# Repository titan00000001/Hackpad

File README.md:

# Arrowpad

My hackpad keyboard is a Macropad to mimic the Arrow keys to be like a controller for keyboard games

## Features
- Can be used as arrows on Keyboard
- Mini Keyboard like design to make it seem like a small keyboard

## Schematics

## PCB

## Assembly

## BOM

| Qty | Part Name               |
|-----|-------------------------|
| 4   | Switches                |
| 4   | Keycaps                 |
| 2   | LEDs                    |
| 1   | Seeed XIAO RP2040       |
| 1   | Case (3d-printed)       |
| 1   | PCB                     |

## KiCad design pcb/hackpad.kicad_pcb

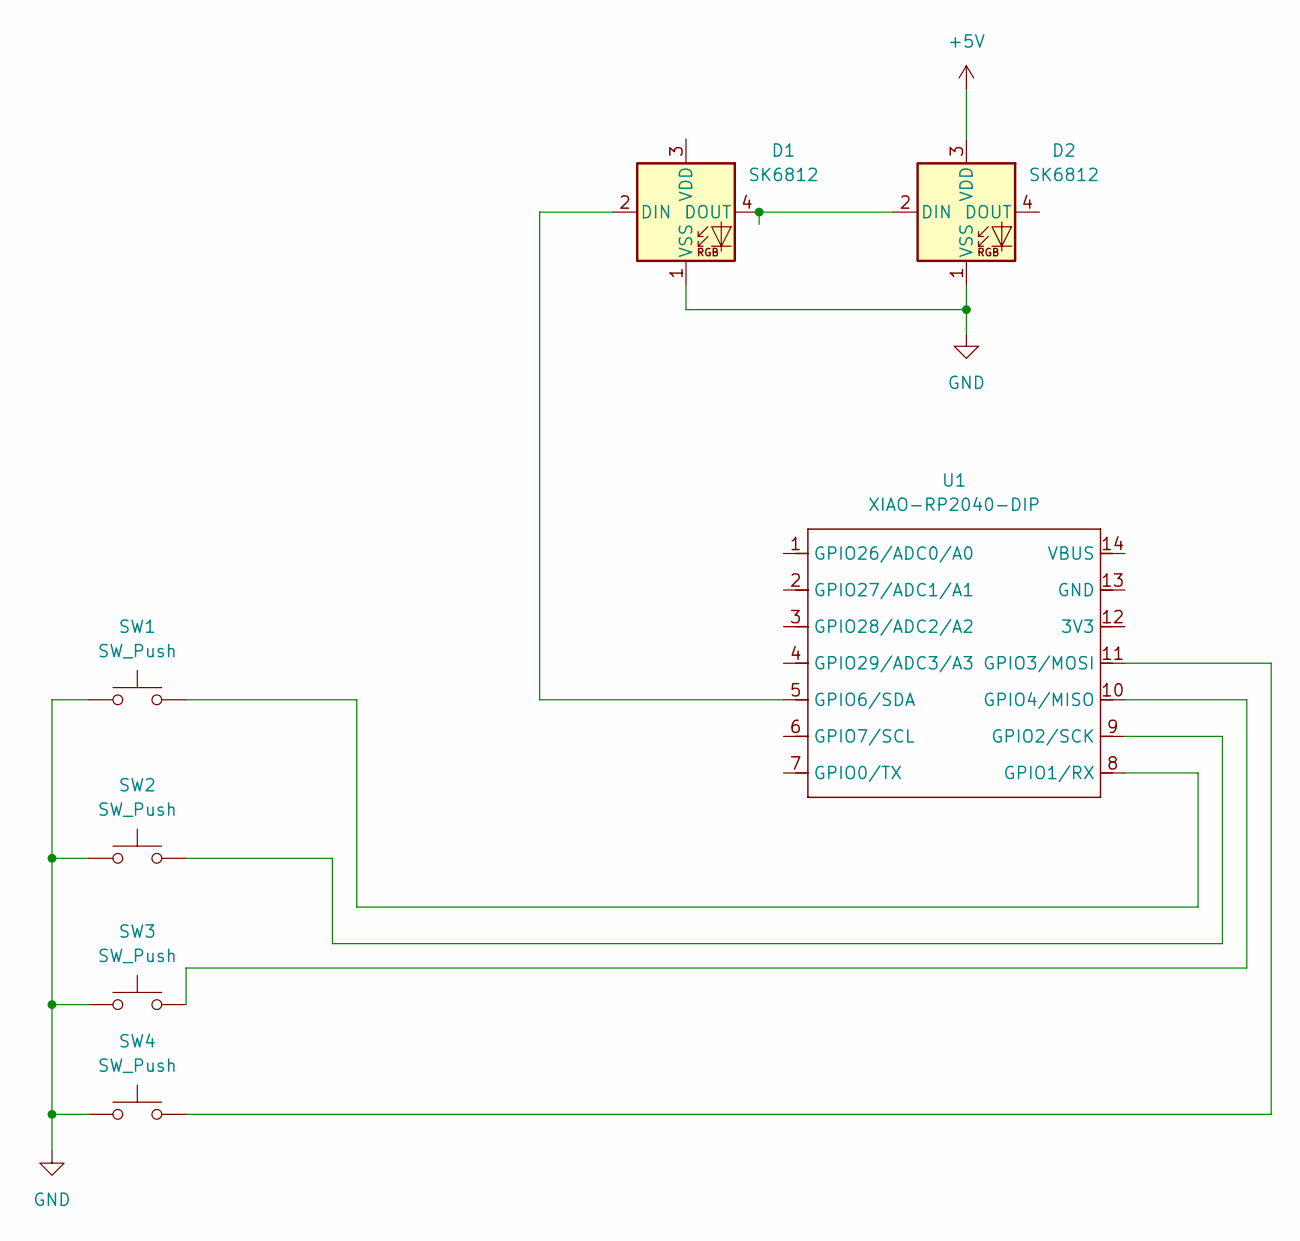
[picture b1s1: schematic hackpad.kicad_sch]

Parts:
D1, D2: SK6812; LED_SK6812_PLCC4_5.0x5.0mm_P3.2mm
SW1, SW2, SW3, SW4: SW_Push; SW_Cherry_MX_1.00u_PCB
U1: XIAO-RP2040-DIP

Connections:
+5V: D2.3 (VDD)
GND: D1.1 (VSS), D2.1 (VSS), SW1.1, SW2.1, SW3.1, SW4.1
unnamed: D1.2 (DIN), U1.5 (GPIO6/SDA)
unnamed: D1.4 (DOUT), D2.2 (DIN)
unnamed: SW1.2, U1.8 (GPIO1/RX)
unnamed: SW2.2, U1.9 (GPIO2/SCK)
unnamed: SW4.2, U1.11 (GPIO3/MOSI)
unnamed: SW3.2, U1.10 (GPIO4/MISO)

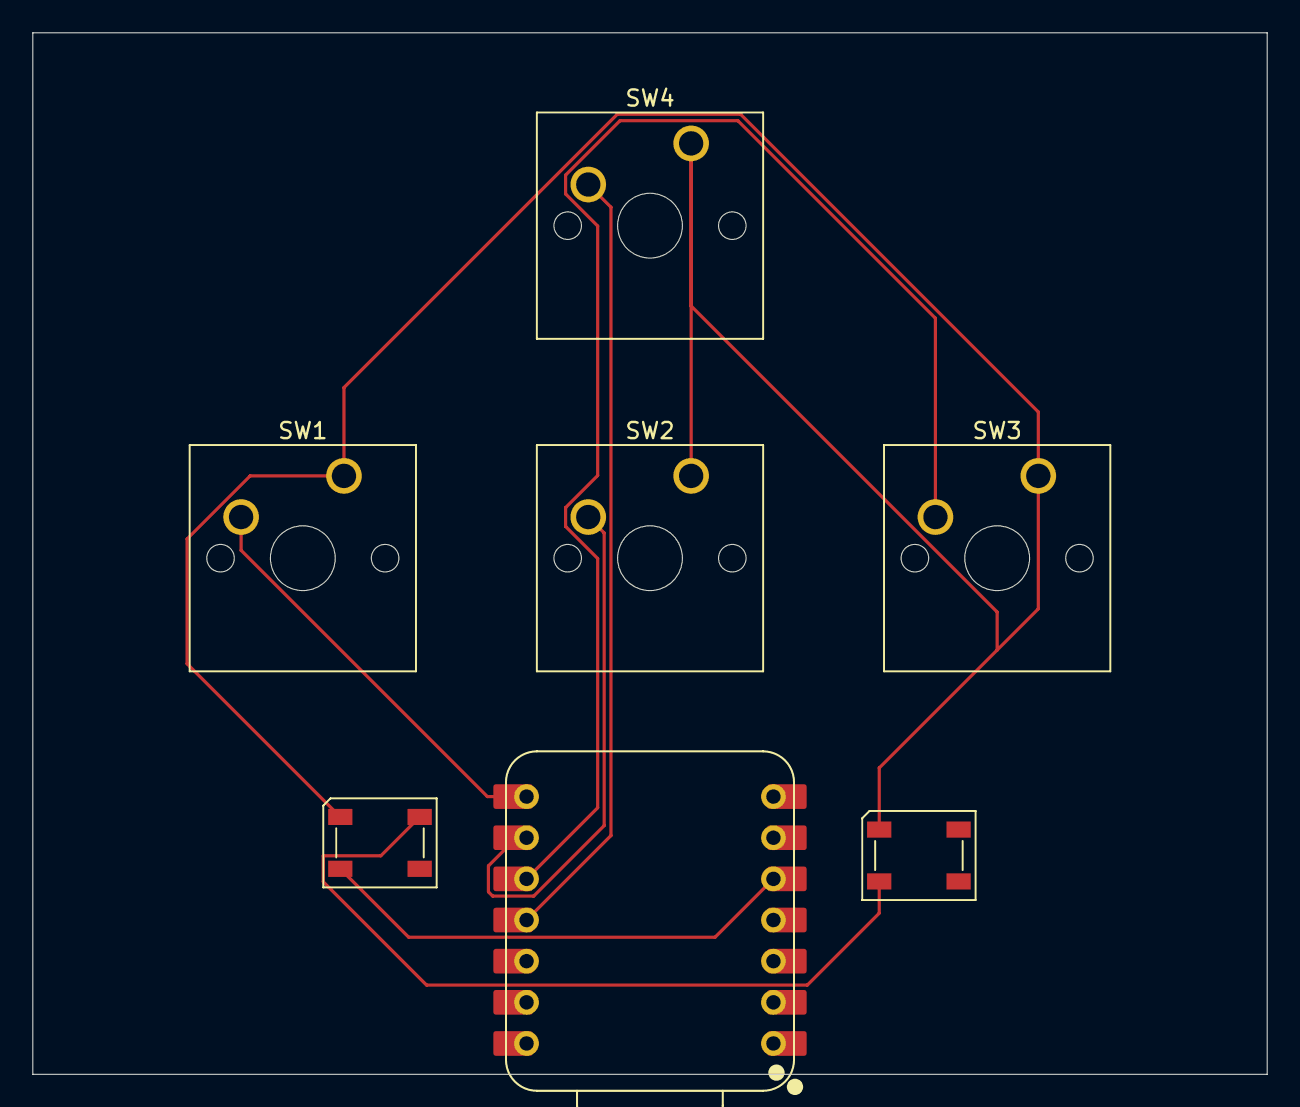
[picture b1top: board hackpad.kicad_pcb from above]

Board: 2 copper layers, 76.2 x 64.3 mm, 7 parts (0 on the bottom side), 7 nets.
